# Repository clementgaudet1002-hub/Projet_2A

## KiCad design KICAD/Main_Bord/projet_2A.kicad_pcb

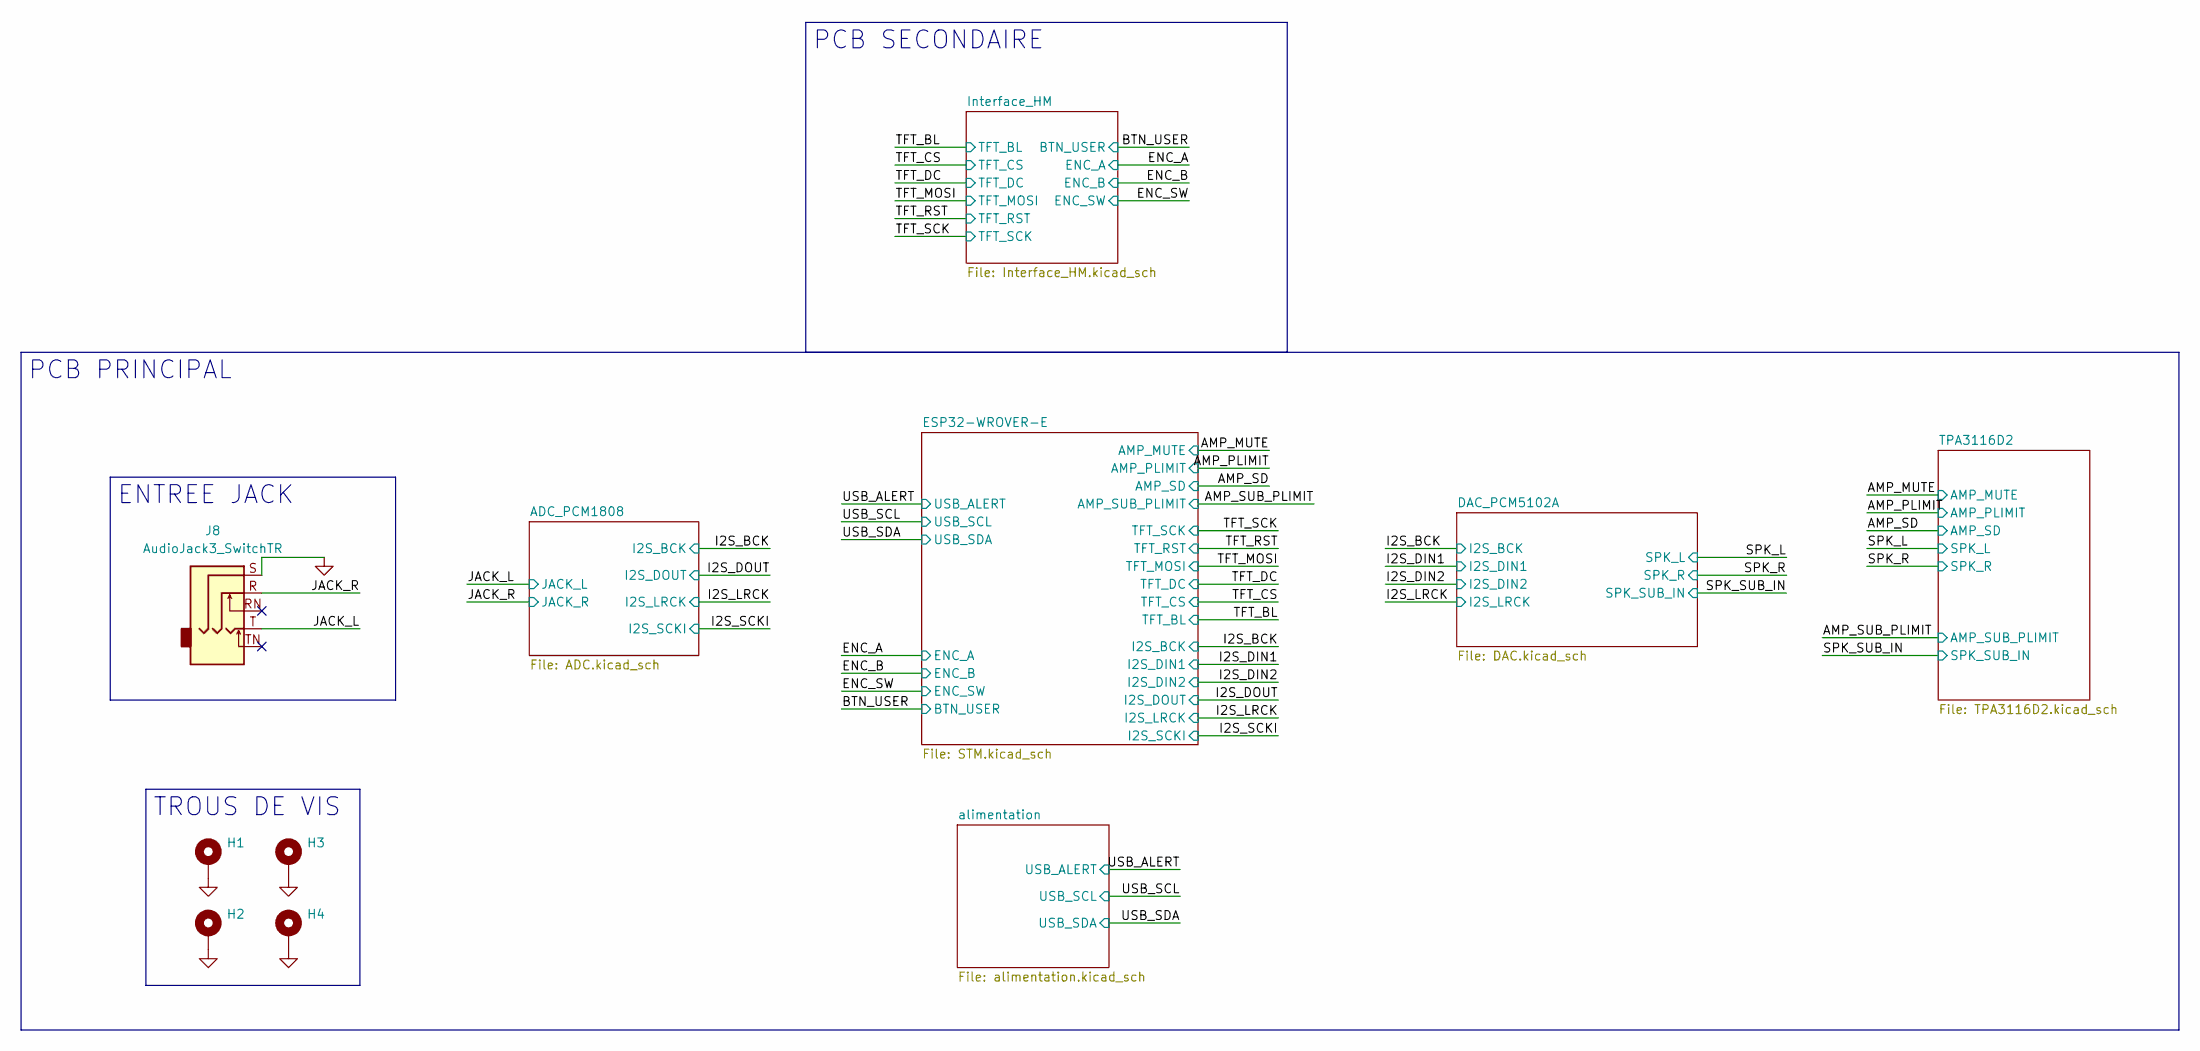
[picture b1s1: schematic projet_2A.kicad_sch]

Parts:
H1, H2, H3, H4: MountingHole_Pad; MountingHole_2.2mm_M2_Pad_TopBottom
J8: AudioJack3_SwitchTR; Jack_3.5mm_Ledino_KB3SPRS_Horizontal

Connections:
/JACK_L: J8.T; also elsewhere on the board
/JACK_R: J8.R; also elsewhere on the board
GND: H1.1 (1_1), H2.1 (1_1), H3.1 (1_1), H4.1 (1_1), J8.S; also elsewhere on the board

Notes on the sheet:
ENTREE JACK
TROUS DE VIS
PCB SECONDAIRE
PCB PRINCIPAL

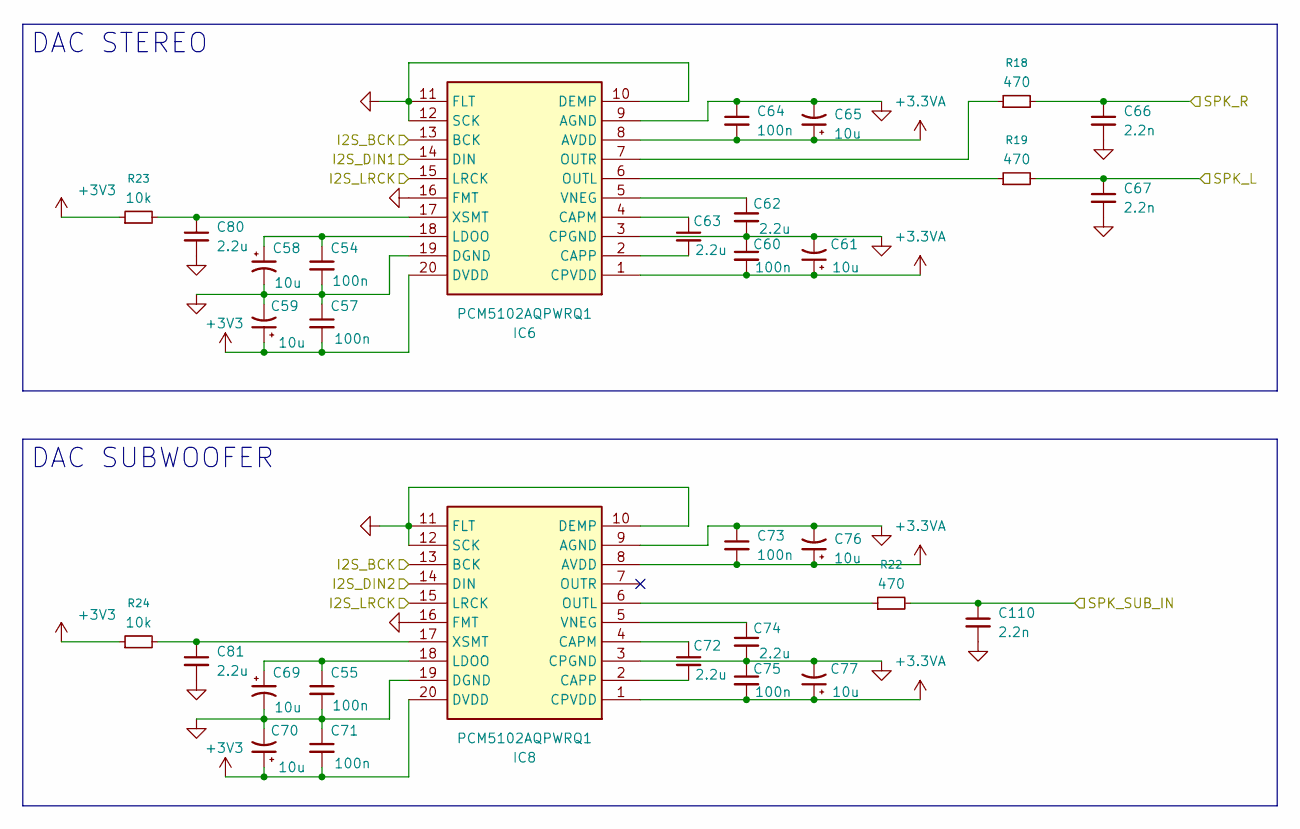
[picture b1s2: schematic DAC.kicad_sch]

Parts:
C54, C55, C57, C60, C64, C71, C73, C75: 100n; C_0603_1608Metric
C58, C59, C61, C65, C69, C70, C76, C77: 10u; C_1206_3216Metric
C62, C63, C72, C74, C80, C81: 2.2u; C_1206_3216Metric
C66, C67, C110: 2.2n; C_0603_1608Metric
IC6, IC8: PCM5102AQPWRQ1; Manufacturer_Part_Number PCM5102AQPWRQ1; Mouser Part Number 595-PCM5102AQPWRQ1
R18, R19, R22: 470; R_0603_1608Metric
R23, R24: 10k; R_0603_1608Metric

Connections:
+3.3VA: C60.2, C61.1, C64.2, C65.1, C73.2, C75.2, C76.1, C77.1, IC6.1 (CPVDD), IC6.8 (AVDD), IC8.1 (CPVDD), IC8.8 (AVDD); also elsewhere on the board
+3V3: C57.2, C59.1, C70.1, C71.2, IC6.20 (DVDD), IC8.20 (DVDD), R23.1, R24.1; also elsewhere on the board
/I2S_BCK: IC6.13 (BCK), IC8.13 (BCK); also elsewhere on the board
/I2S_DIN1: IC6.14 (DIN); also elsewhere on the board
/I2S_DIN2: IC8.14 (DIN); also elsewhere on the board
/I2S_LRCK: IC6.15 (LRCK), IC8.15 (LRCK); also elsewhere on the board
/SPK_L: C67.1, R19.2; also elsewhere on the board
/SPK_R: C66.1, R18.2; also elsewhere on the board
/SPK_SUB_IN: C110.1, R22.2; also elsewhere on the board
GND: C54.2, C55.2, C57.1, C58.2, C59.2, C60.1, C61.2, C62.2, C64.1, C65.2, C66.2, C67.2, C69.2, C70.2, C71.1, C73.1, C74.2, C75.1, C76.2, C77.2, C80.2, C81.2, C110.2, IC6.3 (CPGND), IC6.9 (AGND), IC6.10 (DEMP), IC6.11 (FLT), IC6.12 (SCK), IC6.16 (FMT), IC6.19 (DGND), IC8.3 (CPGND), IC8.9 (AGND), IC8.10 (DEMP), IC8.11 (FLT), IC8.12 (SCK), IC8.16 (FMT), IC8.19 (DGND); also elsewhere on the board
unnamed: C63.1, IC6.4 (CAPM)
unnamed: C63.2, IC6.2 (CAPP)
unnamed: C54.1, C58.1, IC6.18 (LDOO)
unnamed: IC6.6 (OUTL), R19.1
unnamed: IC6.7 (OUTR), R18.1
unnamed: C62.1, IC6.5 (VNEG)
unnamed: C80.1, IC6.17 (XSMT), R23.2
unnamed: C72.1, IC8.4 (CAPM)
unnamed: C72.2, IC8.2 (CAPP)
unnamed: C55.1, C69.1, IC8.18 (LDOO)
unnamed: IC8.6 (OUTL), R22.1
unnamed: C74.1, IC8.5 (VNEG)
unnamed: C81.1, IC8.17 (XSMT), R24.2

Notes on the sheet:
DAC STEREO
DAC SUBWOOFER

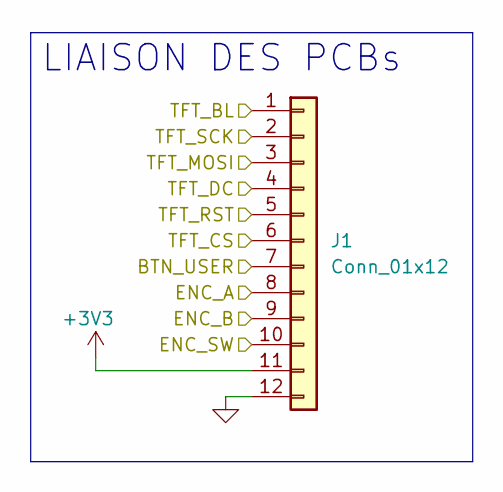
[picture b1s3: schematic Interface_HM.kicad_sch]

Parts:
J1: Conn_01x12; PinHeader_1x12_P2.54mm_Vertical

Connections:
+3V3: J1.11; also elsewhere on the board
/BTN_USER: J1.7; also elsewhere on the board
/ENC_A: J1.8; also elsewhere on the board
/ENC_B: J1.9; also elsewhere on the board
/ENC_SW: J1.10; also elsewhere on the board
/TFT_BL: J1.1; also elsewhere on the board
/TFT_CS: J1.6; also elsewhere on the board
/TFT_DC: J1.4; also elsewhere on the board
/TFT_MOSI: J1.3; also elsewhere on the board
/TFT_RST: J1.5; also elsewhere on the board
/TFT_SCK: J1.2; also elsewhere on the board
GND: J1.12; also elsewhere on the board

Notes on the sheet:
LIAISON DES PCBs

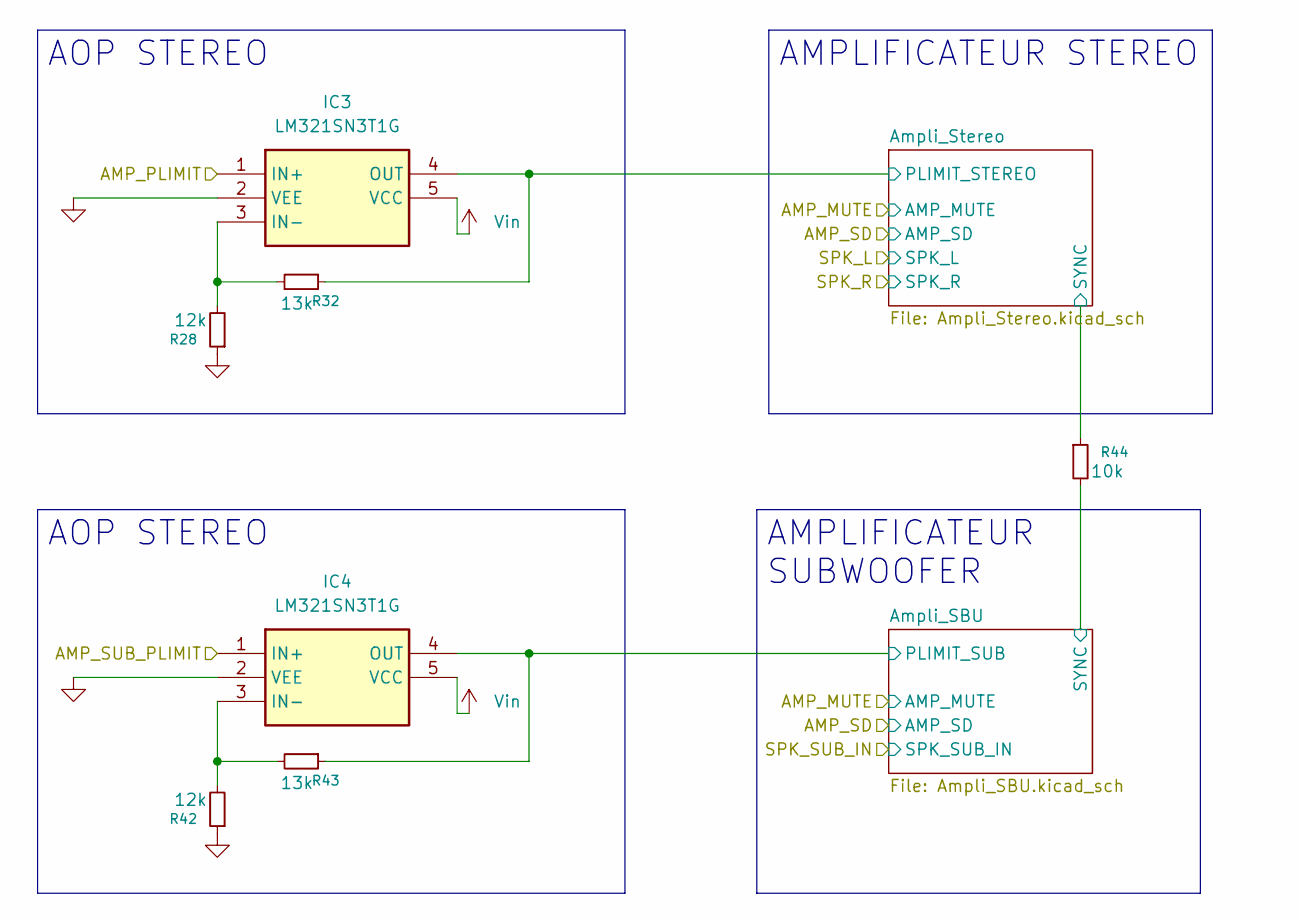
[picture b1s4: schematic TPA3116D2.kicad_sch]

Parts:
IC3, IC4: LM321SN3T1G; Mouser Part Number 863-LM321SN3T1G
R28, R42: 12k; R_0603_1608Metric
R32, R43: 13k; R_0603_1608Metric
R44: 10k; R_0603_1608Metric

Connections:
/AMP_PLIMIT: IC3.1 (IN+); also elsewhere on the board
/AMP_SUB_PLIMIT: IC4.1 (IN+); also elsewhere on the board
/TPA3116D2/Ampli_SBU/PLIMIT_SUB: IC4.4 (OUT), R43.1; also elsewhere on the board
/TPA3116D2/Ampli_SBU/SYNC: R44.2; also elsewhere on the board
/TPA3116D2/Ampli_Stereo/PLIMIT_STEREO: IC3.4 (OUT), R32.1; also elsewhere on the board
/TPA3116D2/Ampli_Stereo/SYNC: R44.1; also elsewhere on the board
GND: IC3.2 (VEE), IC4.2 (VEE), R28.1, R42.1; also elsewhere on the board
unnamed: IC3.3 (IN-), R28.2, R32.2
unnamed: IC4.3 (IN-), R42.2, R43.2
Vin: IC3.5 (VCC), IC4.5 (VCC); also elsewhere on the board

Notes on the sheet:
AMPLIFICATEUR STEREO
AOP STEREO
AMPLIFICATEUR SUBWOOFER

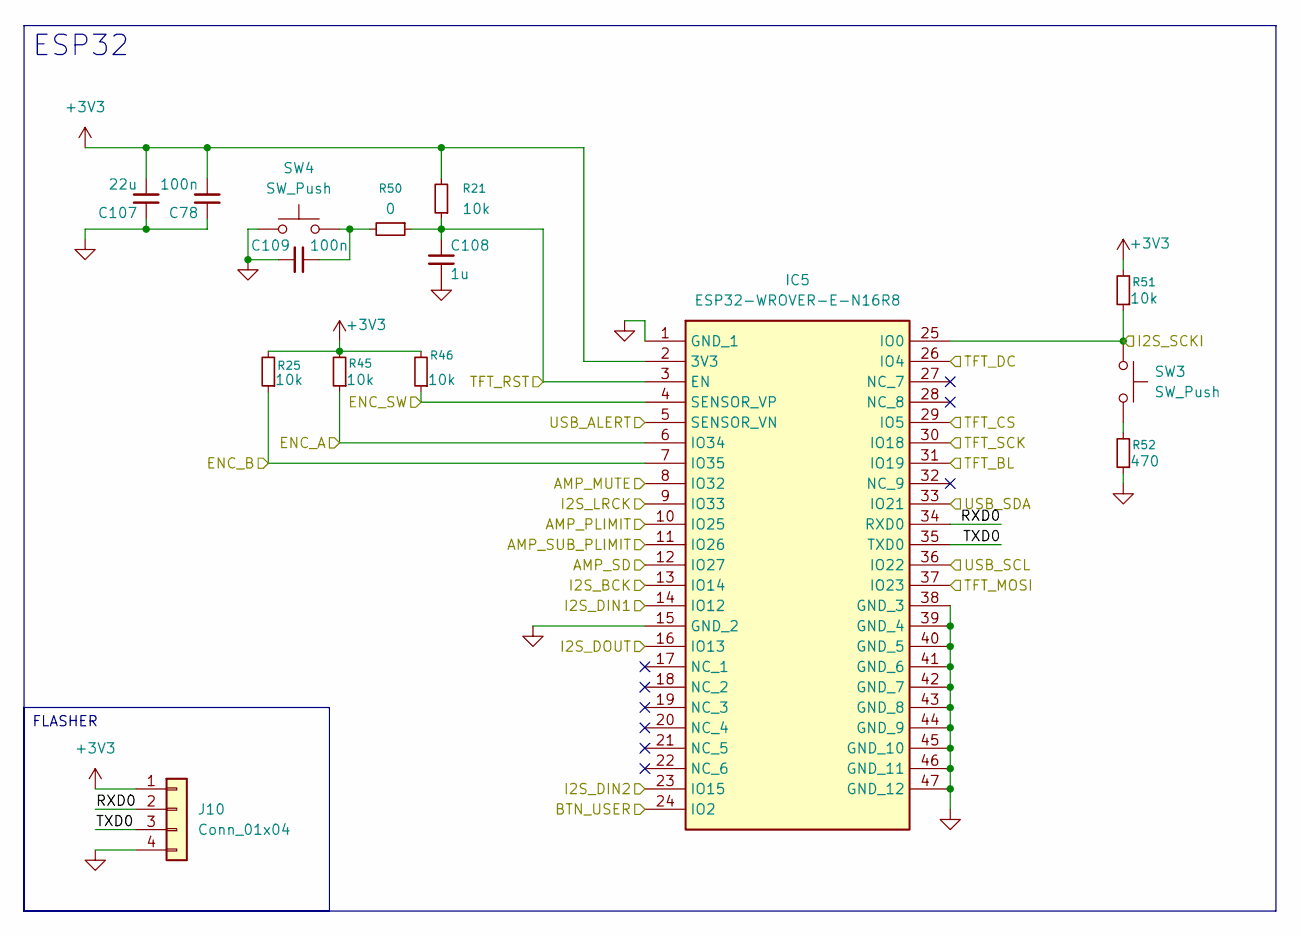
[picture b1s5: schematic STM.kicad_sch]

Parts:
C78, C109: 100n; C_0603_1608Metric
C107: 22u; C_0603_1608Metric
C108: 1u; C_0603_1608Metric
IC5: ESP32-WROVER-E-N16R8; ESP32WROVEREN16R8; Mouser Part Number 356-ESP32WRVE22864PC
J10: Conn_01x04; PinHeader_1x04_P2.54mm_Vertical
R21, R25, R45, R46, R51: 10k; R_0603_1608Metric
R50: 0; R_0603_1608Metric
R52: 470; R_0603_1608Metric
SW3, SW4: SW_Push; SW_Push_1P1T_NO_CK_KMR2

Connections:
+3V3: C78.2, C107.2, IC5.2 (3V3), J10.1, R21.2, R25.2, R45.2, R46.2, R51.2; also elsewhere on the board
/AMP_MUTE: IC5.8 (IO32); also elsewhere on the board
/AMP_PLIMIT: IC5.10 (IO25); also elsewhere on the board
/AMP_SD: IC5.12 (IO27); also elsewhere on the board
/AMP_SUB_PLIMIT: IC5.11 (IO26); also elsewhere on the board
/BTN_USER: IC5.24 (IO2); also elsewhere on the board
/ENC_A: IC5.6 (IO34), R45.1; also elsewhere on the board
/ENC_B: IC5.7 (IO35), R25.1; also elsewhere on the board
/ENC_SW: IC5.4 (SENSOR_VP), R46.1; also elsewhere on the board
/ESP32-WROVER-E/RXD0: IC5.34 (RXD0), J10.2
/ESP32-WROVER-E/TXD0: IC5.35 (TXD0), J10.3
/I2S_BCK: IC5.13 (IO14); also elsewhere on the board
/I2S_DIN1: IC5.14 (IO12); also elsewhere on the board
/I2S_DIN2: IC5.23 (IO15); also elsewhere on the board
/I2S_DOUT: IC5.16 (IO13); also elsewhere on the board
/I2S_LRCK: IC5.9 (IO33); also elsewhere on the board
/I2S_SCKI: IC5.25 (IO0), R51.1, SW3.1; also elsewhere on the board
/TFT_BL: IC5.31 (IO19); also elsewhere on the board
/TFT_CS: IC5.29 (IO5); also elsewhere on the board
/TFT_DC: IC5.26 (IO4); also elsewhere on the board
/TFT_MOSI: IC5.37 (IO23); also elsewhere on the board
/TFT_RST: C108.1, IC5.3 (EN), R21.1, R50.1; also elsewhere on the board
/TFT_SCK: IC5.30 (IO18); also elsewhere on the board
/USB_ALERT: IC5.5 (SENSOR_VN); also elsewhere on the board
/USB_SCL: IC5.36 (IO22); also elsewhere on the board
/USB_SDA: IC5.33 (IO21); also elsewhere on the board
GND: C78.1, C107.1, C108.2, C109.2, IC5.1 (GND_1), IC5.15 (GND_2), IC5.38 (GND_3), IC5.39 (GND_4), IC5.40 (GND_5), IC5.41 (GND_6), IC5.42 (GND_7), IC5.43 (GND_8), IC5.44 (GND_9), IC5.45 (GND_10), IC5.46 (GND_11), IC5.47 (GND_12), J10.4, R52.1, SW4.1; also elsewhere on the board
unnamed: C109.1, R50.2, SW4.2
unnamed: R52.2, SW3.2

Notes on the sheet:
FLASHER
ESP32

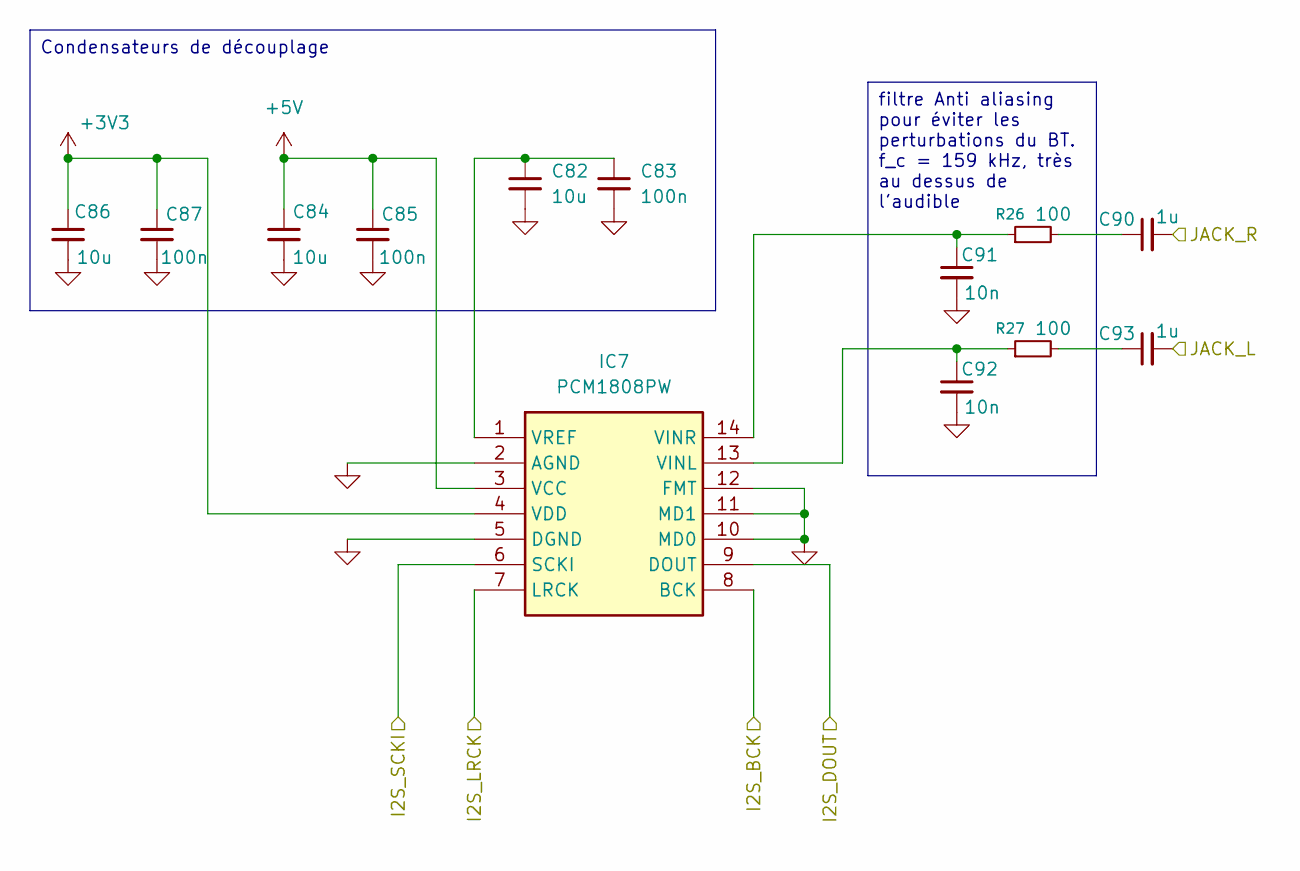
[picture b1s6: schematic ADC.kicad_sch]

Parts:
C82, C84, C86: 10u; C_1206_3216Metric
C83, C85, C87: 100n; C_0603_1608Metric
C90, C93: 1u; C_0603_1608Metric
C91, C92: 10n; C_0603_1608Metric
IC7: PCM1808PW; Manufacturer_Part_Number PCM1808PW; Mouser Part Number 595-PCM1808PW
R26, R27: 100; R_0603_1608Metric

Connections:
+3V3: C86.1, C87.1, IC7.4 (VDD); also elsewhere on the board
+5V: C84.1, C85.1, IC7.3 (VCC); also elsewhere on the board
/I2S_BCK: IC7.8 (BCK); also elsewhere on the board
/I2S_DOUT: IC7.9 (DOUT); also elsewhere on the board
/I2S_LRCK: IC7.7 (LRCK); also elsewhere on the board
/I2S_SCKI: IC7.6 (SCKI); also elsewhere on the board
/JACK_L: C93.2; also elsewhere on the board
/JACK_R: C90.2; also elsewhere on the board
GND: C82.2, C83.2, C84.2, C85.2, C86.2, C87.2, C91.2, C92.2, IC7.2 (AGND), IC7.5 (DGND), IC7.10 (MD0), IC7.11 (MD1), IC7.12 (FMT); also elsewhere on the board
unnamed: C90.1, R26.2
unnamed: C93.1, R27.2
unnamed: C92.1, IC7.13 (VINL), R27.1
unnamed: C91.1, IC7.14 (VINR), R26.1
unnamed: C82.1, C83.1, IC7.1 (VREF)

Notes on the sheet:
filtre Anti aliasing pour éviter les perturbations du BT. f_c = 159 kHz, très au dessus de l'audible
Condensateurs de découplage

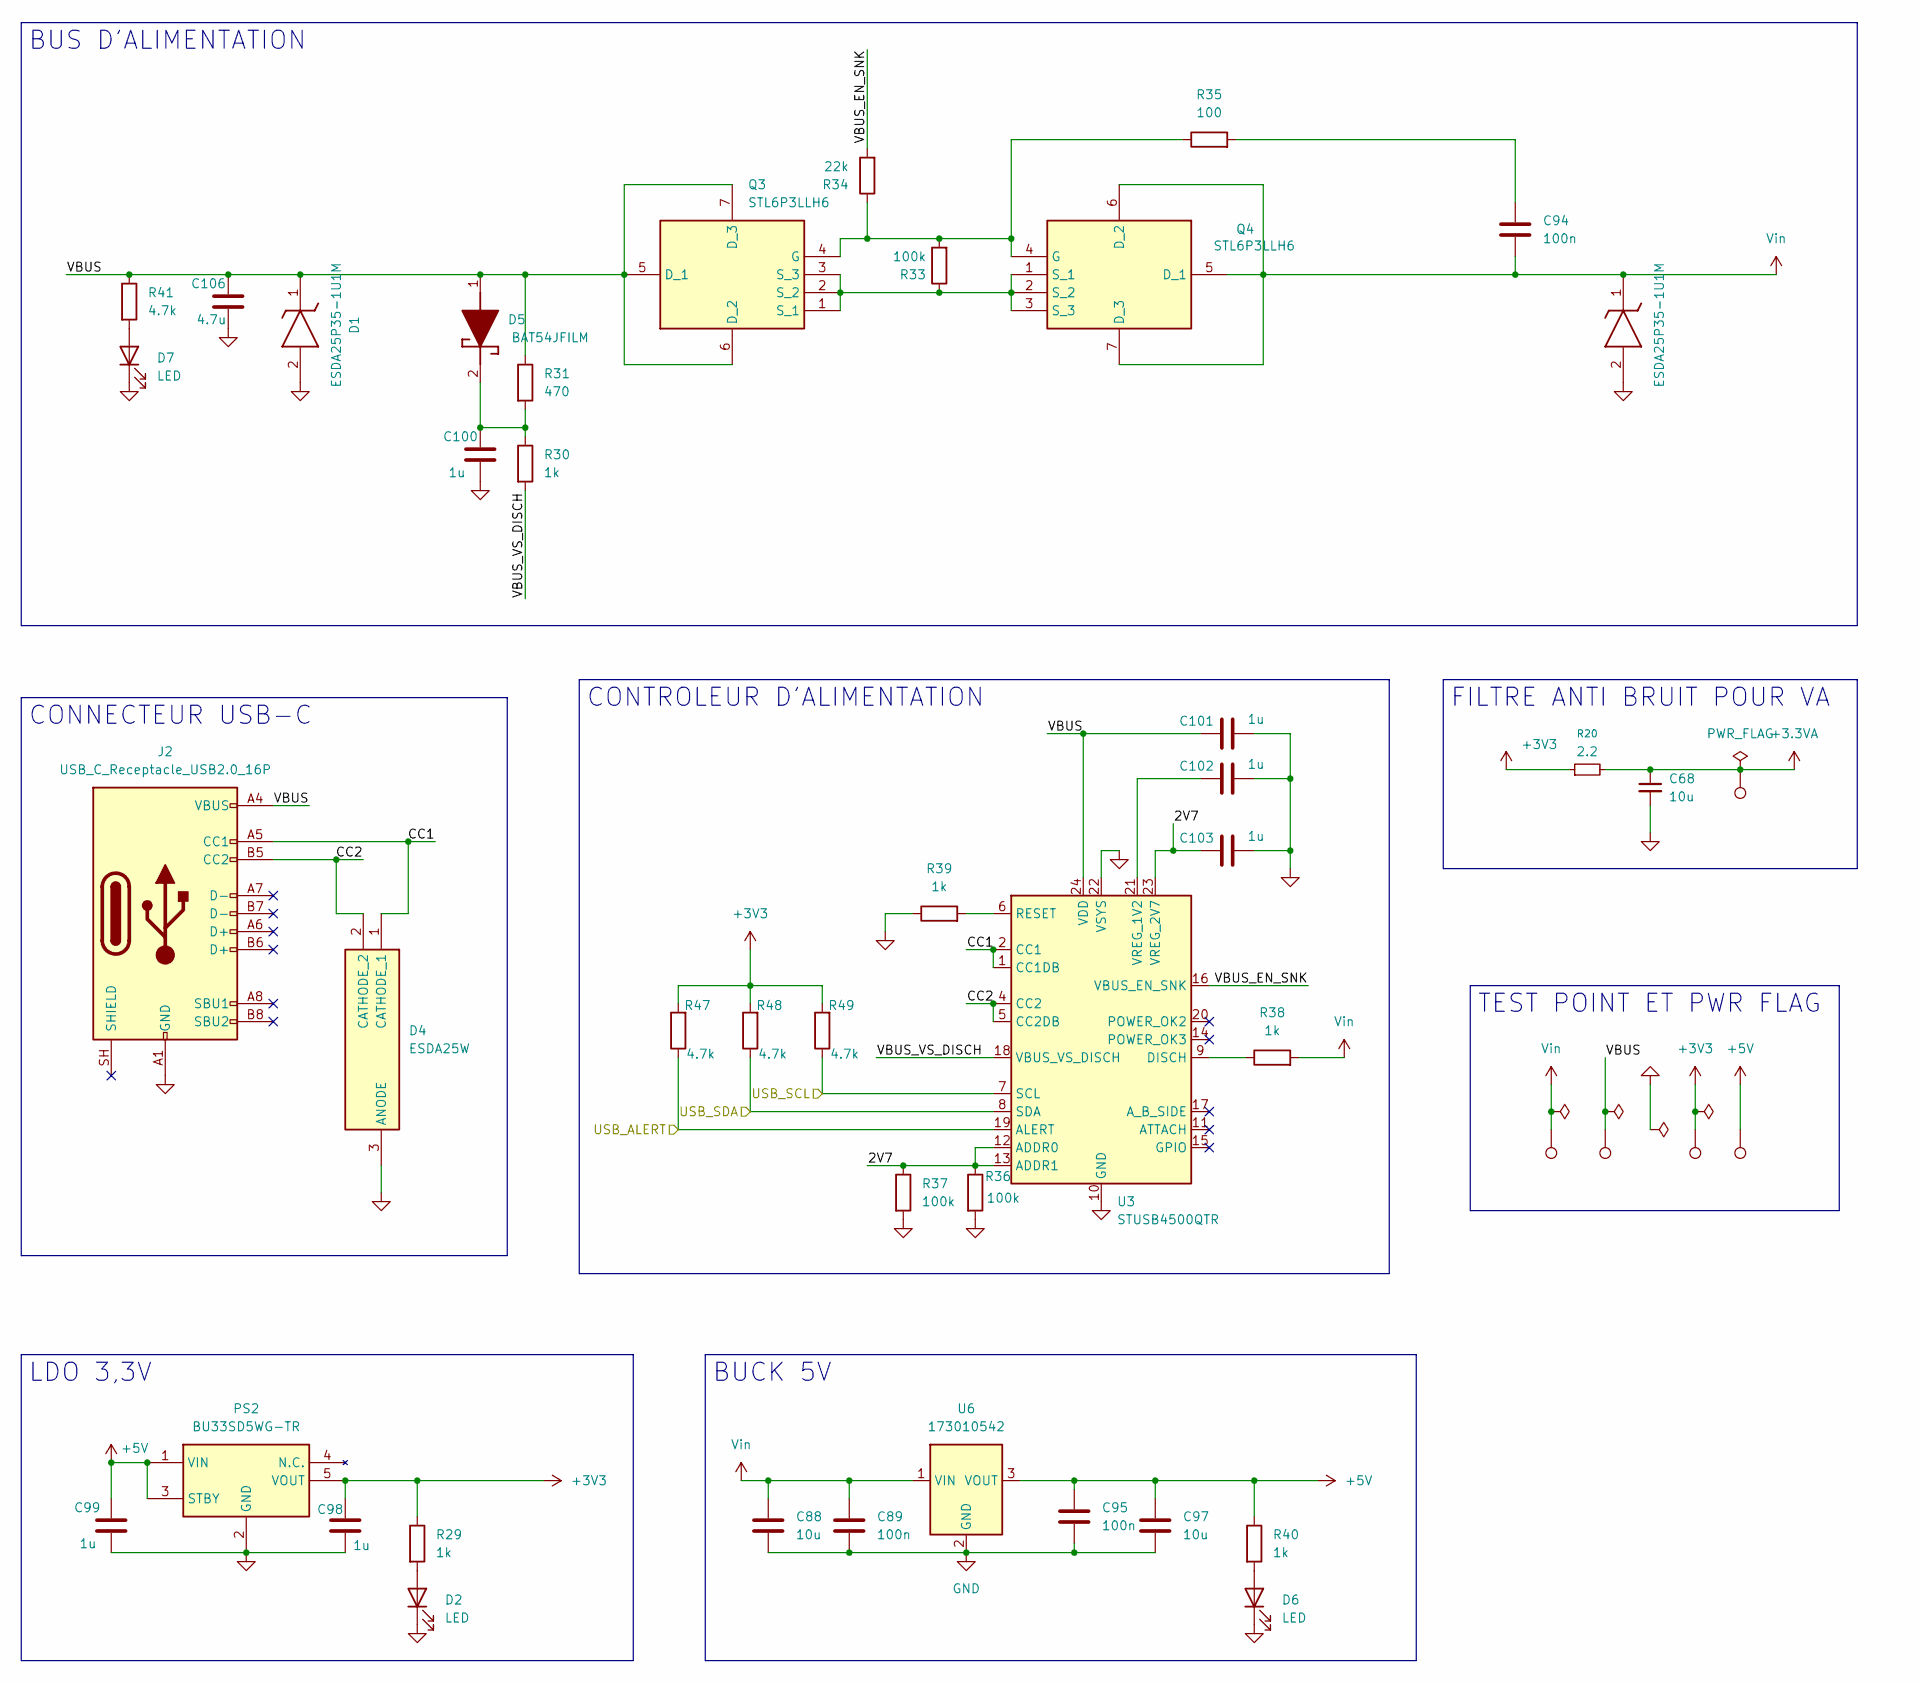
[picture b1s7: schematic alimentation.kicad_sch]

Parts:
C68, C88, C97: 10u; C_1206_3216Metric
C89, C94, C95: 100n; C_0603_1608Metric
C98, C99, C100, C101, C102, C103: 1u; C_0603_1608Metric
C106: 4.7u; C_0603_1608Metric
D1, D3: ESDA25P35-1U1M; ESDA25P351U1M; Mouser Part Number 511-ESDA25P35-1U1M
D2, D6, D7: LED; LED_0603_1608Metric
D4: ESDA25W; Mouser Part Number 511-ESDA25W
D5: BAT54JFILM; Mouser Part Number 511-BAT54JFILM
J2: USB_C_Receptacle_USB2.0_16P; USB_C_Receptacle_GCT_USB4105-xx-A_16P_TopMnt_Horizontal
PS2: BU33SD5WG-TR; Manufacturer_Part_Number BU33SD5WG-TR; Mouser Part Number 755-BU33SD5WG-TR
Q3, Q4: STL6P3LLH6; STL8N10F7; Mouser Part Number 511-STL6P3LLH6
R20: 2.2; R_0603_1608Metric
R29, R30, R38, R39, R40: 1k; R_0603_1608Metric
R31: 470; R_0603_1608Metric
R33, R36, R37: 100k; R_0603_1608Metric
R34: 22k; R_0603_1608Metric
R35: 100; R_0603_1608Metric
R41: 4.7k; R_1206_3216Metric
R47, R48, R49: 4.7k; R_0603_1608Metric
TP2, TP4, TP6, TP7, TP8: TestPoint; TestPoint_Pad_D1.5mm
U3: STUSB4500QTR; QFN-24-1EP_4x4mm_P0.5mm_EP2.7x2.7mm
U6: 173010542; U_Wurth_MagIC-FDSM_173010x42

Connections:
+3.3VA: C68.1, R20.2, TP8.1 (1_1); also elsewhere on the board
+3V3: C98.1, PS2.5 (VOUT), R20.1, R29.1, R47.2, R48.2, R49.2, TP6.1 (1_1); also elsewhere on the board
+5V: C95.1, C97.1, C99.1, PS2.1 (VIN), PS2.3 (STBY), R40.1, TP7.1 (1_1), U6.3 (VOUT); also elsewhere on the board
/USB_ALERT: R47.1, U3.19 (ALERT); also elsewhere on the board
/USB_SCL: R49.1, U3.7 (SCL); also elsewhere on the board
/USB_SDA: R48.1, U3.8 (SDA); also elsewhere on the board
/alimentation/2V7: C103.1, R36.1, R37.1, U3.12 (ADDR0), U3.13 (ADDR1), U3.23 (VREG_2V7)
/alimentation/CC1: D4.1 (CATHODE_1), J2.A5 (CC1), U3.1 (CC1DB), U3.2 (CC1)
/alimentation/CC2: D4.2 (CATHODE_2), J2.B5 (CC2), U3.4 (CC2), U3.5 (CC2DB)
/alimentation/VBUS: C101.1, C106.1, D1.1 (K), D5.1 (A), J2.A4 (VBUS), J2.A9 (VBUS), J2.B4 (VBUS), J2.B9 (VBUS), Q3.5 (D_1), Q3.6 (D_2), Q3.7 (D_3), R31.1, R41.1, TP4.1 (1_1), U3.24 (VDD)
/alimentation/VBUS_EN_SNK: R34.2, U3.16 (VBUS_EN_SNK)
/alimentation/VBUS_VS_DISCH: R30.2, U3.18 (VBUS_VS_DISCH)
GND: C68.2, C88.2, C89.2, C95.2, C97.2, C98.2, C99.2, C100.2, C101.2, C102.2, C103.2, C106.2, D1.2 (A), D2.1 (K), D3.2 (A), D4.3 (ANODE), D6.1 (K), D7.1 (K), J2.A1 (GND), J2.A12 (GND), J2.B1 (GND), J2.B12 (GND), PS2.2 (GND), R36.2, R37.2, R39.1, U3.10 (GND), U3.22 (VSYS), U3.25 (GND), U6.2 (GND); also elsewhere on the board
unnamed: C94.2, R35.2
unnamed: D2.2 (A), R29.2
unnamed: C100.1, D5.2 (K), R30.1, R31.2
unnamed: D6.2 (A), R40.2
unnamed: D7.2 (A), R41.2
unnamed: Q3.4 (G), Q4.4 (G), R33.2, R34.1, R35.1
unnamed: Q3.1 (S_1), Q3.2 (S_2), Q3.3 (S_3), Q4.1 (S_1), Q4.2 (S_2), Q4.3 (S_3), R33.1
unnamed: R38.1, U3.9 (DISCH)
unnamed: R39.2, U3.6 (RESET)
unnamed: C102.1, U3.21 (VREG_1V2)
Vin: C88.1, C89.1, C94.1, D3.1 (K), Q4.5 (D_1), Q4.6 (D_2), Q4.7 (D_3), R38.2, TP2.1 (1_1), U6.1 (VIN); also elsewhere on the board

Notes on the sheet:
CONTROLEUR D'ALIMENTATION
TEST POINT ET PWR FLAG
FILTRE ANTI BRUIT POUR VA
BUCK 5V
BUS D'ALIMENTATION
LDO 3,3V
CONNECTEUR USB-C

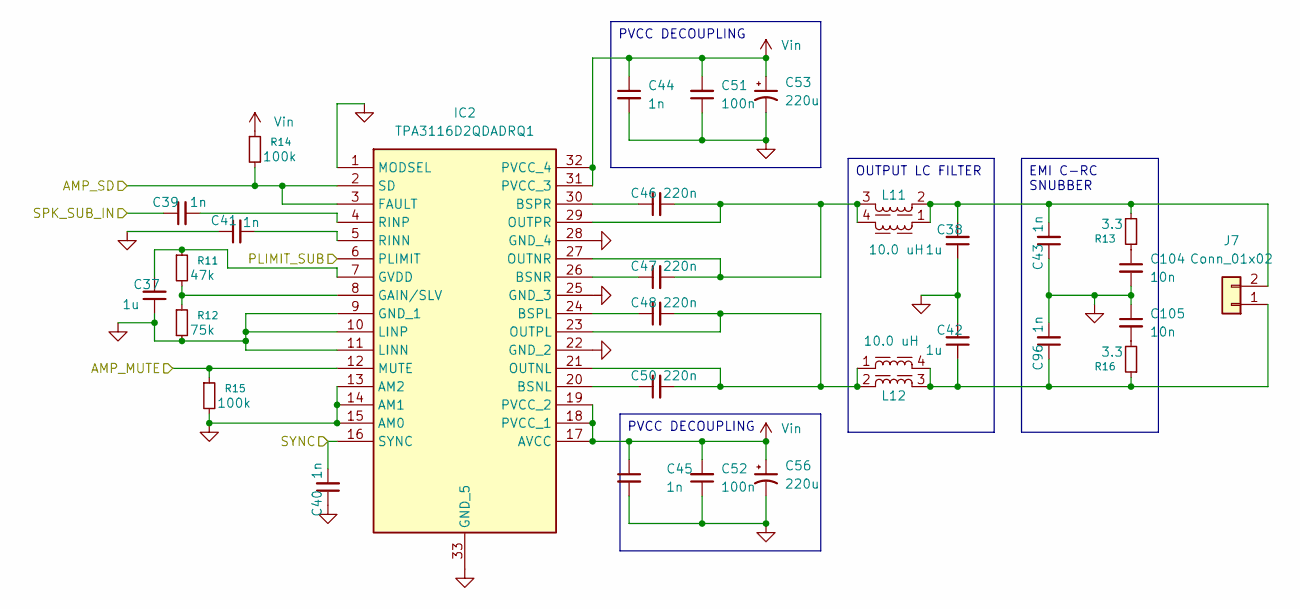
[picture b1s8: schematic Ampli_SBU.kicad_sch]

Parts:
C37, C38, C42: 1u; C_0603_1608Metric
C39, C40, C41, C43, C44, C45, C96: 1n; C_0603_1608Metric
C46, C47, C48, C50: 220n; C_0603_1608Metric
C51, C52: 100n; C_0603_1608Metric
C53, C56: 220u; CP_Radial_D6.3mm_P2.50mm
C104, C105: 10n; C_0603_1608Metric
IC2: TPA3116D2QDADRQ1; Mouser Part Number 595-TPA3116D2QDADRQ1
J7: Conn_01x02; TerminalBlock_Phoenix_MKDS-1,5-2-5.08_1x02_P5.08mm_Horizont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
L11, L12: 10.0 uH; L_Wurth_WE-LHMD-1213; Part Number 74434301213100
R11: 47k; R_0603_1608Metric
R12: 75k; R_0603_1608Metric
R13, R16: 3.3; R_0603_1608Metric
R14, R15: 100k; R_0603_1608Metric

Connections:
/AMP_MUTE: IC2.12 (MUTE), R15.1; also elsewhere on the board
/AMP_SD: IC2.2 (SD), IC2.3 (FAULT), R14.2; also elsewhere on the board
/SPK_SUB_IN: C39.1; also elsewhere on the board
/TPA3116D2/Ampli_SBU/PLIMIT_SUB: IC2.6 (PLIMIT); also elsewhere on the board
/TPA3116D2/Ampli_SBU/SYNC: C40.2, IC2.16 (SYNC); also elsewhere on the board
GND: C37.1, C38.1, C40.1, C41.1, C42.2, C43.1, C44.2, C45.2, C51.1, C52.1, C53.2, C56.2, C96.2, C104.2, C105.1, IC2.1 (MODSEL), IC2.9 (GND_1), IC2.10 (LINP), IC2.11 (LINN), IC2.13 (AM2), IC2.14 (AM1), IC2.15 (AM0), IC2.22 (GND_2), IC2.25 (GND_3), IC2.28 (GND_4), IC2.33 (GND_5), R12.2, R15.2; also elsewhere on the board
unnamed: C104.1, R13.1
unnamed: C105.2, R16.2
unnamed: C50.1, IC2.20 (BSNL)
unnamed: C47.1, IC2.26 (BSNR)
unnamed: C48.1, IC2.24 (BSPL)
unnamed: C46.1, IC2.30 (BSPR)
unnamed: IC2.8 (GAIN/SLV), R11.2, R12.1
unnamed: C37.2, IC2.7 (GVDD), R11.1
unnamed 79: C48.2, C50.2, IC2.21 (OUTNL), IC2.23 (OUTPL), L12.1, L12.2; also elsewhere on the board
unnamed 80: C46.2, C47.2, IC2.27 (OUTNR), IC2.29 (OUTPR), L11.3, L11.4; also elsewhere on the board
unnamed: C41.2, IC2.5 (RINN)
unnamed: C39.2, IC2.4 (RINP)
unnamed 105: C42.1, C96.1, J7.1, L12.3, L12.4, R16.1; also elsewhere on the board
unnamed 106: C38.2, C43.2, J7.2, L11.1, L11.2, R13.2; also elsewhere on the board
Vin: C44.1, C45.1, C51.2, C52.2, C53.1, C56.1, IC2.17 (AVCC), IC2.18 (PVCC_1), IC2.19 (PVCC_2), IC2.31 (PVCC_3), IC2.32 (PVCC_4), R14.1; also elsewhere on the board

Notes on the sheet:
PVCC DECOUPLING
OUTPUT LC FILTER
EMI C-RC SNUBBER

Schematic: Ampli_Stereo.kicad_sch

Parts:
C1, C4, C16: 100n; C_0603_1608Metric
C2, C26, C27, C28, C29: 10n; C_0603_1608Metric
C3, C6, C7, C9, C10, C15, C20, C22, C24, C25: 1n; C_0603_1608Metric
C5, C17: 220u; CP_Radial_D6.3mm_P2.50mm
C8: 1u; C_0603_1608Metric
C11, C12, C13, C14: 220n; C_0603_1608Metric
C18, C19, C21, C23: 680n; C_0603_1608Metric
IC1: TPA3116D2QDADRQ1; Mouser Part Number 595-TPA3116D2QDADRQ1
J5, J6: Conn_01x02; TerminalBlock_Phoenix_MKDS-1,5-2-5.08_1x02_P5.08mm_Horizont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
L1, L2, L3, L4: 7447706100; Mouser Part Number 710-7447706100
R1, R3, R5: 100k; R_0603_1608Metric
R2, R6, R7, R8, R9: 3.3; R_0603_1608Metric
R4: 20k; R_0603_1608Metric

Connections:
/AMP_MUTE: IC1.12 (MUTE), R5.1; also elsewhere on the board
/AMP_SD: IC1.2 (SD), IC1.3 (FAULT), R1.2; also elsewhere on the board
/SPK_L: C9.1; also elsewhere on the board
/SPK_R: C6.1; also elsewhere on the board
/TPA3116D2/Ampli_Stereo/PLIMIT_STEREO: IC1.6 (PLIMIT); also elsewhere on the board
/TPA3116D2/Ampli_Stereo/SYNC: IC1.16 (SYNC); also elsewhere on the board
GND: C1.2, C2.1, C3.2, C4.1, C5.2, C7.1, C8.1, C10.1, C15.2, C16.1, C17.2, C18.2, C19.1, C20.1, C21.2, C22.2, C23.1, C24.2, C25.1, C26.2, C27.1, C28.1, C29.2, IC1.1 (MODSEL), IC1.9 (GND_1), IC1.13 (AM2), IC1.14 (AM1), IC1.15 (AM0), IC1.22 (GND_2), IC1.25 (GND_3), IC1.28 (GND_4), IC1.33 (GND_5), R4.2, R5.2; also elsewhere on the board
unnamed: C1.1, R2.2
unnamed: C26.1, R8.1
unnamed: C27.2, R9.2
unnamed: C28.2, R7.2
unnamed: C29.1, R6.1
unnamed: C14.1, IC1.20 (BSNL)
unnamed: C12.1, IC1.26 (BSNR)
unnamed: C13.1, IC1.24 (BSPL)
unnamed: C11.1, IC1.30 (BSPR)
unnamed: IC1.8 (GAIN/SLV), R3.2, R4.1
unnamed: C8.2, IC1.7 (GVDD), R3.1
unnamed: C10.2, IC1.11 (LINN)
unnamed: C9.2, IC1.10 (LINP)
unnamed: C14.2, IC1.21 (OUTNL), L4.1
unnamed: C12.2, IC1.27 (OUTNR), L2.1
unnamed: C13.2, IC1.23 (OUTPL), L3.2
unnamed: C11.2, IC1.29 (OUTPR), L1.2
unnamed: C7.2, IC1.5 (RINN)
unnamed: C6.2, IC1.4 (RINP)
unnamed: C19.2, C20.2, J5.1, L2.2, R7.1
unnamed: C18.1, C22.1, J5.2, L1.1, R6.2
unnamed: C23.2, C25.2, J6.1, L4.2, R9.1
unnamed: C21.1, C24.1, J6.2, L3.1, R8.2
Vin: C2.2, C3.1, C4.2, C5.1, C15.1, C16.2, C17.1, IC1.17 (AVCC), IC1.18 (PVCC_1), IC1.19 (PVCC_2), IC1.31 (PVCC_3), IC1.32 (PVCC_4), R1.1, R2.1; also elsewhere on the board

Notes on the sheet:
PVCC DECOUPLING
OUTPUT LC FILTER
EMI C-RC SNUBBER
